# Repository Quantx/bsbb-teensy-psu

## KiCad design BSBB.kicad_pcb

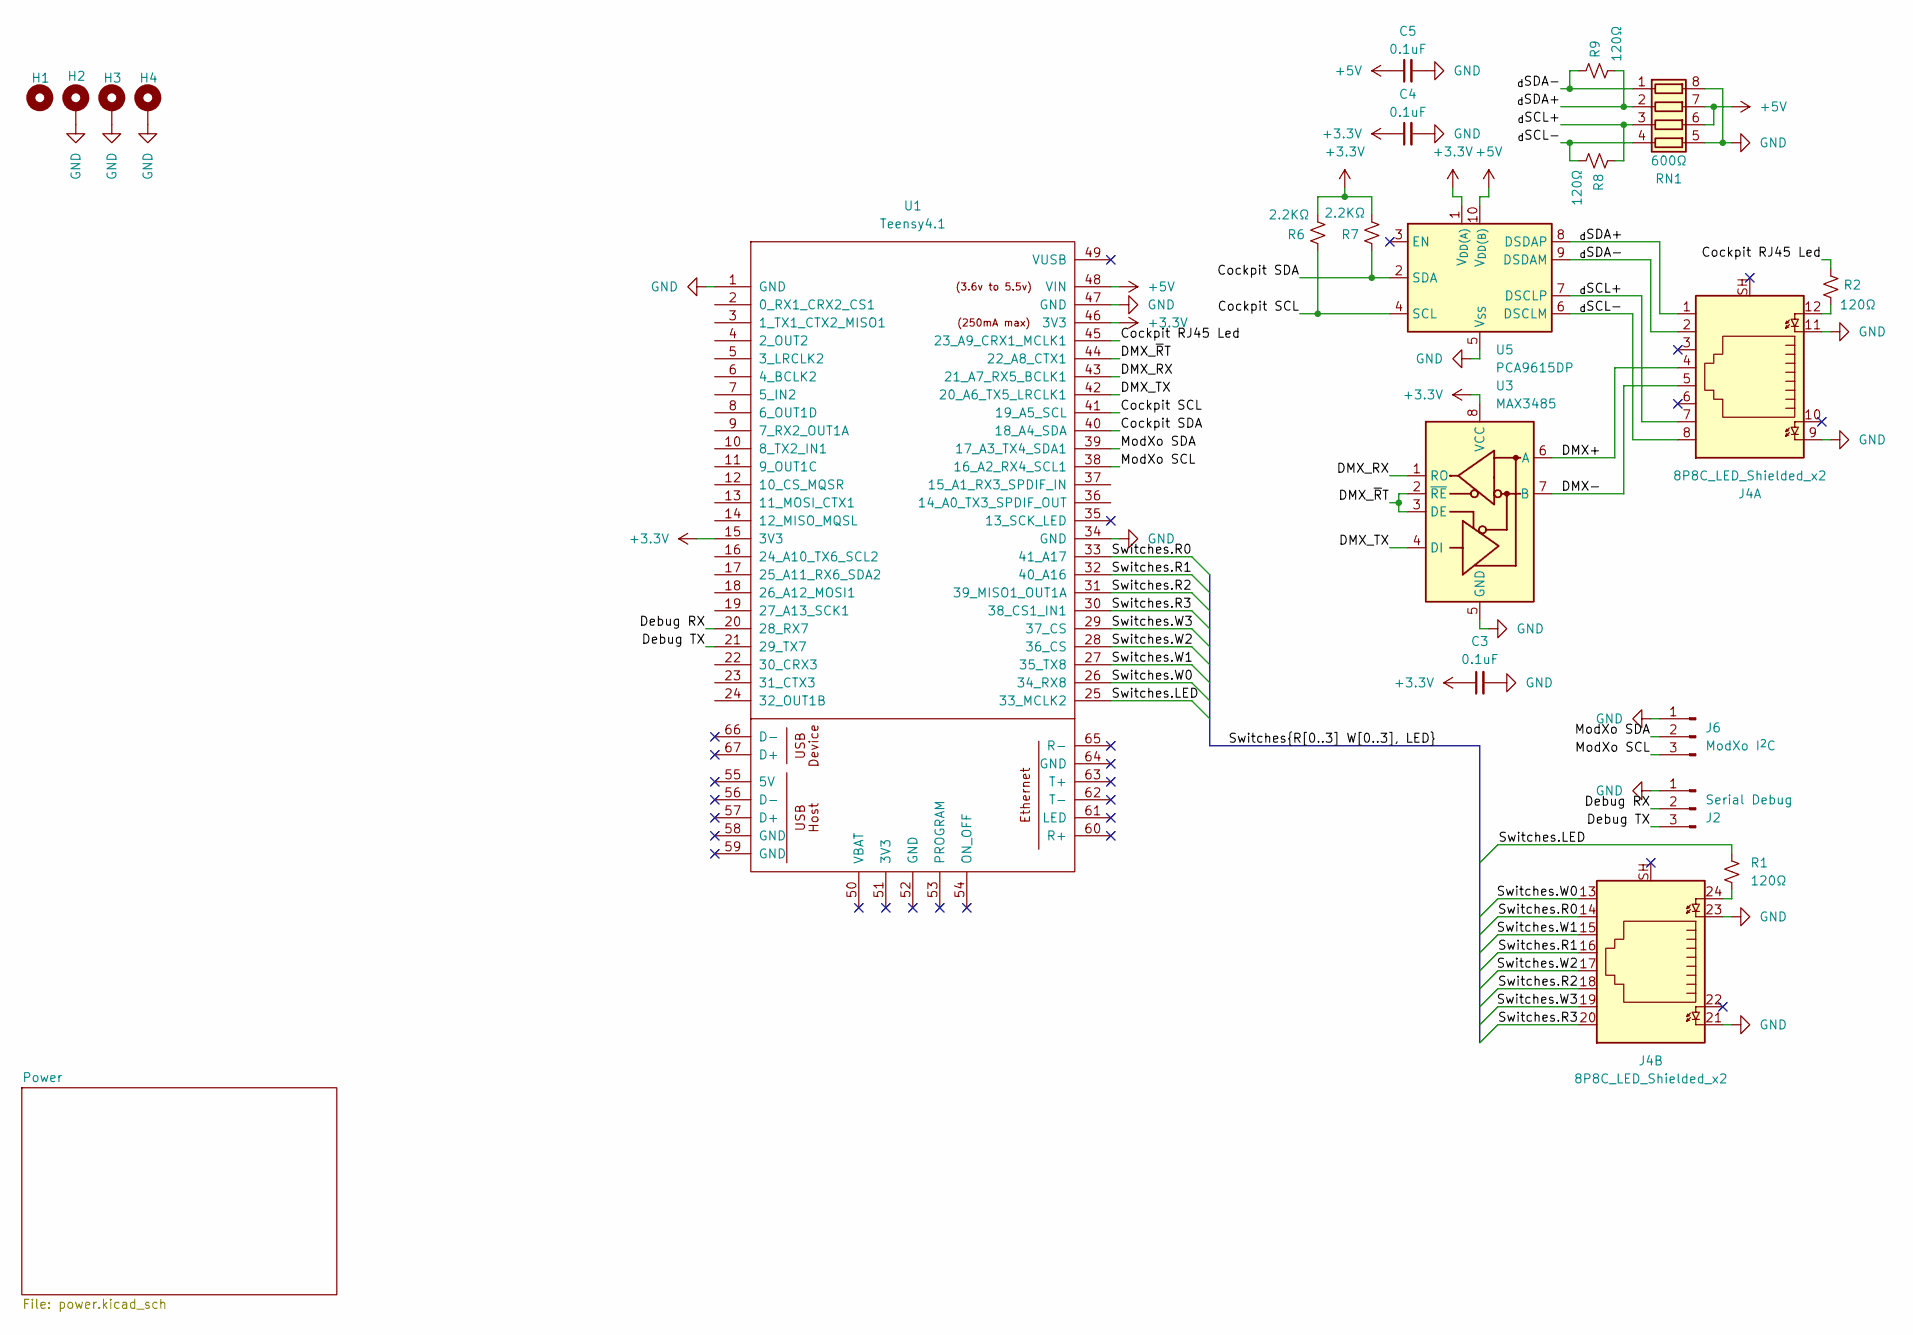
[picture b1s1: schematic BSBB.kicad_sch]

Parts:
C3, C5: 0.1uF; C_0603_1608Metric_Pad1.08x0.95mm_HandSolder; LCSC C6119867
C4: 0.1uF; C_0603_1608Metric_Pad1.08x0.95mm_HandSolder
H1: MountingHole; MountingHole_4.3mm_M4
H2, H3: MountingHole; MountingHole_4.3mm_M4_Pad
H4: MountingHole; MountingHole_4.3mm_M4_ISO7380_Pad
J2: Serial Debug; PinHeader_1x03_P2.54mm_Vertical
J4: 8P8C_LED_Shielded_x2; RJ45_Amphenol_RJHSE538X-02
J6: ModXo I^{2}C; PinHeader_1x03_P2.54mm_Vertical
R1, R2, R8, R9: 120Ω; R_0603_1608Metric_Pad0.98x0.95mm_HandSolder; LCSC C2906988
R6, R7: 2.2KΩ; R_0603_1608Metric_Pad0.98x0.95mm_HandSolder; LCSC C2907005
RN1: 600Ω; R_Array_Convex_4x0603; LCSC C48580704
U1: Teensy4.1; Teensy41
U3: MAX3485; SOIC-8_3.9x4.9mm_P1.27mm; LCSC C668204
U5: PCA9615DP; TSSOP-10_3x3mm_P0.5mm; LCSC C3824272

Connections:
+3.3V: C3.1, C4.1, R6.1, R7.1, U1.15 (3V3), U1.46 (3V3), U3.8 (VCC), U5.1 (V_{DD(A)})
+5V: C5.1, RN1.6 (R3.2), RN1.7 (R2.2), U1.48 (VIN), U5.10 (V_{DD(B)}); also elsewhere on the board
/Cockpit RJ45 Led: R2.2, U1.45 (23_A9_CRX1_MCLK1)
/Cockpit SCL: R6.2, U1.41 (19_A5_SCL), U5.4 (SCL)
/Cockpit SDA: R7.2, U1.40 (18_A4_SDA), U5.2 (SDA)
/DMX+: J4.4, U3.6 (A)
/DMX-: J4.5, U3.7 (B)
/DMX_RX: U1.43 (21_A7_RX5_BCLK1), U3.1 (RO)
/DMX_TX: U1.42 (20_A6_TX5_LRCLK1), U3.4 (DI)
/DMX_~RT: U1.44 (22_A8_CTX1), U3.2 (~RE), U3.3 (DE)
/Debug RX: J2.2, U1.20 (28_RX7)
/Debug TX: J2.3, U1.21 (29_TX7)
/ModXo SCL: J6.3, U1.38 (16_A2_RX4_SCL1)
/ModXo SDA: J6.2, U1.39 (17_A3_TX4_SDA1)
/Switches.LED: R1.2, U1.25 (33_MCLK2)
/Switches.R0: J4.14, U1.33 (41_A17)
/Switches.R1: J4.16, U1.32 (40_A16)
/Switches.R2: J4.18, U1.31 (39_MISO1_OUT1A)
/Switches.R3: J4.20, U1.30 (38_CS1_IN1)
/Switches.W0: J4.13, U1.26 (34_RX8)
/Switches.W1: J4.15, U1.27 (35_TX8)
/Switches.W2: J4.17, U1.28 (36_CS)
/Switches.W3: J4.19, U1.29 (37_CS)
/_{d}SCL+: J4.7, R8.2, RN1.3 (R3.1), U5.7 (DSCLP)
/_{d}SCL-: J4.8, R8.1, RN1.4 (R4.1), U5.6 (DSCLM)
/_{d}SDA+: J4.1, R9.1, RN1.2 (R2.1), U5.8 (DSDAP)
/_{d}SDA-: J4.2, R9.2, RN1.1 (R1.1), U5.9 (DSDAM)
GND: C3.2, C4.2, C5.2, H2.1 (1_1), H3.1 (1_1), H4.1 (1_1), J2.1, J4.9, J4.11, J4.21, J4.23, J6.1, RN1.5 (R4.2), RN1.8 (R1.2), U1.1 (GND), U1.34 (GND), U1.47 (GND), U3.5 (GND), U5.5 (V_{SS}); also elsewhere on the board
unnamed: J4.12, R2.1
unnamed: J4.24, R1.1

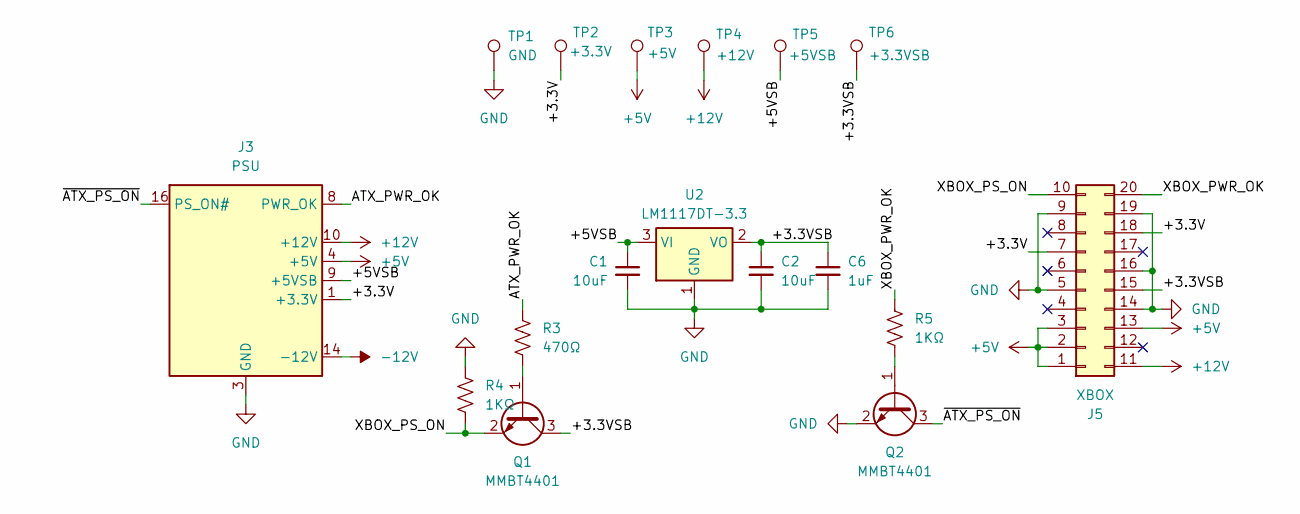
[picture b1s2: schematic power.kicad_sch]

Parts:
C1, C2: 10uF; C_0603_1608Metric_Pad1.08x0.95mm_HandSolder; LCSC C19702
C6: 1uF; C_0603_1608Metric_Pad1.08x0.95mm_HandSolder; LCSC C15849
J3: PSU; Molex_Mini-Fit_Jr_5566-24A_2x12_P4.20mm_Vertical
J5: XBOX; Molex_Mini-Fit_Jr_5566-20A_2x10_P4.20mm_Vertical
Q1, Q2: MMBT4401; SOT-23; LCSC C31776
R3: 470Ω; R_0603_1608Metric_Pad0.98x0.95mm_HandSolder; LCSC C114433
R4, R5: 1KΩ; R_0603_1608Metric_Pad0.98x0.95mm_HandSolder; LCSC C2907113
TP1: GND; TestPoint_Keystone_5010-5014_Multipurpose
TP2: +3.3V; TestPoint_Keystone_5010-5014_Multipurpose
TP3: +5V; TestPoint_Keystone_5010-5014_Multipurpose
TP4: +12V; TestPoint_Keystone_5010-5014_Multipurpose
TP5: +5VSB; TestPoint_Keystone_5010-5014_Multipurpose
TP6: +3.3VSB; TestPoint_Keystone_5010-5014_Multipurpose
U2: LM1117DT-3.3; TO-252-3_TabPin2; LCSC C129952

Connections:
+5V: J3.4 (+5V), J3.6 (+5V), J3.21 (+5V), J3.22 (+5V), J3.23 (+5V), J5.1, J5.2, J5.3, J5.13, TP3.1 (1_1); also elsewhere on the board
+12V: J3.10 (+12V), J3.11 (+12V), J5.11, TP4.1 (1_1)
-12V: J3.14 (-12V)
/Power/+3.3V: J3.1 (+3.3V), J3.2 (+3.3V), J3.12 (+3.3V), J3.13 (+3.3V), J5.7, J5.18, TP2.1 (1_1)
/Power/+3.3VSB: C2.1, C6.1, J5.15, Q1.3 (C), TP6.1 (1_1), U2.2 (VO)
/Power/+5VSB: C1.1, J3.9 (+5VSB), TP5.1 (1_1), U2.3 (VI)
/Power/ATX_PWR_OK: J3.8 (PWR_OK), R3.1
/Power/XBOX_PS_ON: J5.10, Q1.2 (E), R4.2
/Power/XBOX_PWR_OK: J5.20, R5.2
/Power/~ATX_PS_ON: J3.16 (PS_ON#), Q2.3 (C)
GND: C1.2, C2.2, C6.2, J3.3 (GND), J3.5 (GND), J3.7 (GND), J3.15 (GND), J3.17 (GND), J3.18 (GND), J3.19 (GND), J3.24 (GND), J5.5, J5.9, J5.14, J5.16, J5.19, Q2.2 (E), R4.1, TP1.1 (1_1), U2.1 (GND); also elsewhere on the board
unnamed: Q1.1 (B), R3.2
unnamed: Q2.1 (B), R5.1

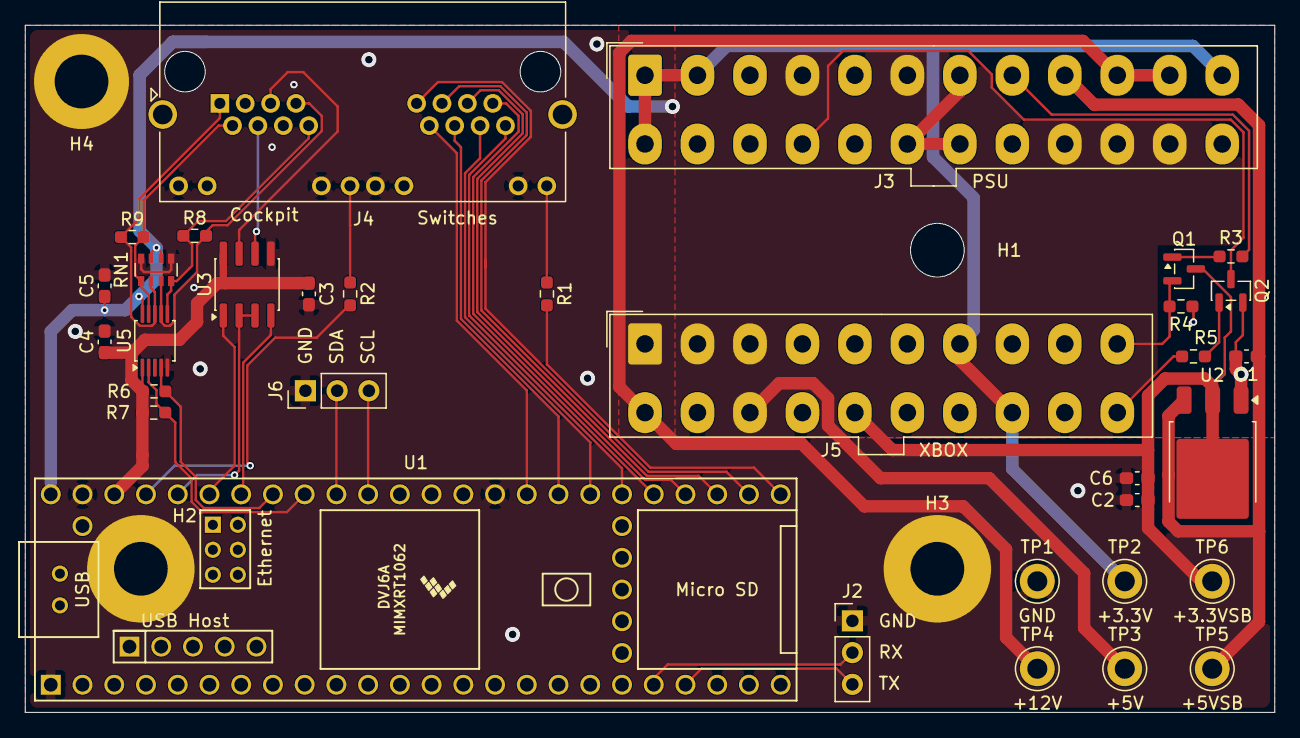
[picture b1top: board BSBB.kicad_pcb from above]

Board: 2 copper layers, 100.0 x 55.0 mm, 37 parts (0 on the bottom side), 40 nets.
